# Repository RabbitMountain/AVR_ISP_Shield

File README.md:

(Rabbit Mountain Research) AVR ISP Shield
========================

This shield, once assembled, gives your Arduino a 28-pin ZIF (Zero Insertion Force) socket so it can grab onto unsuspecting ICs. 
The socket and ISP headers are wired to work directly with the ArduinoISP code.

This is a slightly modified clone of the Evil Mad Scientist AVR ISP Shield v2.0. This version is built on the Sparkfun AVR ISP Shield Eagle files, but is more or less an exact clone of the Evil Mad Scientist Shield.

Rabbit Mountain Research changes
-------------------
* converted EvilMadScience design from gEDA to Autodesk EagleCAD
* fixed the non-working "hello" LED
* added 5v / 3v VCC power select jumper (taken from Sparkfun's ISP Shield design)
* added 0.1uF reset capacitor for UNO / 328p Arduino compatibility

Repository Contents
-------------------
* **/Hardware** - All Eagle design files (.brd, .sch)

License Information
-------------------
The hardware is released under [Creative Commons ShareAlike 4.0 International](https://creativecommons.org/licenses/by-sa/4.0/).
Sparkfun Electronics

&

Distributed under the [TAPR Open Hardware License](www.tapr.org/OHL).
Evil Mad Science LCC

Distributed as-is; no warranty is given.

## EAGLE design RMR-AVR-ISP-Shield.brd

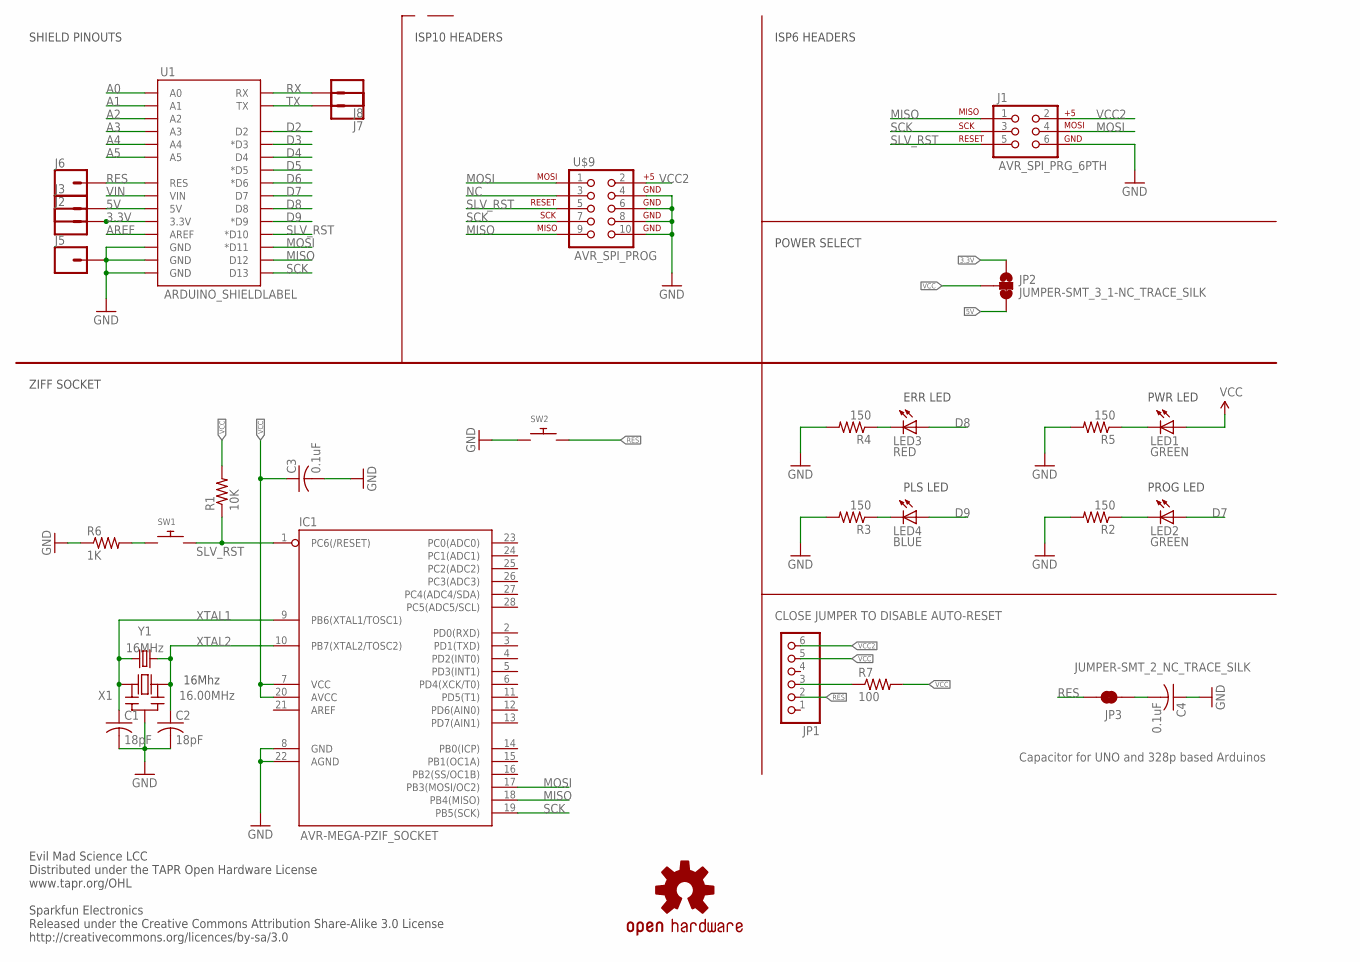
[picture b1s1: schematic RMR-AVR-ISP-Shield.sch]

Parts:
C1, C2: 18pF; C025-024X044
C3, C4: 0.1uF; C025-024X044
IC1: AVR-MEGA-PZIF_SOCKET; DIL28-3-ZIF_SOCKET
J1: AVR_SPI_PRG_6PTH; 2X3
J2, J3, J5, J6, J7, J8: CONN_01; 1X01
JP1: PINHD-1X6/90; 1X06/90
JP2: JUMPER-SMT_3_1-NC_TRACE_SILK; SMT-JUMPER_3_1-NC_TRACE_SILK
JP3: JUMPER-SMT_2_NC_TRACE_SILK; SMT-JUMPER_2_NC_TRACE_SILK
LED1, LED2: GREEN; LED3MM
LED3: RED; LED3MM
LED4: BLUE; LED3MM
R1: 10K; AXIAL-0.4
R2, R3, R4, R5: 150; AXIAL-0.4
R6: 1K; AXIAL-0.4
R7: 100; AXIAL-0.4
SW1, SW2: SWITCH_PUSHBUTTONEVQ-PE; TACT_PANA-EVQ
U1: ARDUINO_SHIELDLABEL; DUEMILANOVE_SHIELD
U$4: OSHW-LOGOM; OSHW-LOGO-M
U$9: AVR_SPI_PROG; AVR_ICSP
X1: 16.00MHz; CERM_OSC
Y1: 16MHz; HC49US

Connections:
3.3V: J2.1, JP2.1, U1.3.3V
5V: J3.1, JP2.3, U1.5V
A0: U1.A0
A1: U1.A1
A2: U1.A2
A3: U1.A3
A4: U1.A4
A5: U1.A5
AREF: U1.AREF
D2: U1.D2
D3: U1.D3 (*D3)
D4: U1.D4
D5: U1.D5 (*D5)
D6: U1.D6 (*D6)
D7: LED2.A, U1.D7
D8: LED3.A, U1.D8
D9: LED4.A, U1.D9 (*D9)
GND: C1.2, C2.2, C3.2, C4.1, IC1.8 (GND), IC1.22 (AGND), J1.6, J5.1, R2.P$2 (2), R3.P$2 (2), R4.P$2 (2), R5.P$2 (2), R6.P$1 (1), SW2.P$1, U1.GND@0 (GND), U1.GND@1 (GND), U1.GND@2 (GND), U$9.4, U$9.6, U$9.8, U$9.10, X1.P$2 (GND)
MISO: IC1.18 (PB4(MISO)), J1.1, U1.D12, U$9.9
MOSI: IC1.17 (PB3(MOSI/OC2)), J1.4, U1.D11 (*D11), U$9.1
unnamed: R6.P$2 (2), SW1.P$1
unnamed: LED2.K (C), R2.P$1 (1)
unnamed: LED3.K (C), R4.P$1 (1)
unnamed: LED1.K (C), R5.P$1 (1)
unnamed: JP1.3, R7.P$1 (1)
unnamed: LED4.K (C), R3.P$1 (1)
unnamed: C4.2, JP3.1
NC: U$9.3
RES: J6.1, JP1.2, JP3.2, SW2.P$2, U1.RES
RX: J8.1, U1.RX
SCK: IC1.19 (PB5(SCK)), J1.3, U1.D13, U$9.7
SLV_RST: IC1.1 (PC6(/RESET)), J1.5, R1.P$1 (1), SW1.P$2, U1.D10 (*D10), U$9.5
TX: J7.1, U1.TX
VCC: C3.1, IC1.7 (VCC), IC1.20 (AVCC), JP1.5, JP2.2, LED1.A, R1.P$2 (2), R7.P$2 (2)
VCC2: J1.2, JP1.6, U$9.2
VIN: U1.VIN
XTAL1: C1.1, IC1.9 (PB6(XTAL1/TOSC1)), X1.P$1 (IN), Y1.1
XTAL2: C2.1, IC1.10 (PB7(XTAL2/TOSC2)), X1.P$3 (OUT), Y1.2

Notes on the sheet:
PWR LED
PROG LED
ISP6 HEADERS
ERR LED
PLS LED
16Mhz
Evil Mad Science LCC Distributed under the TAPR Open Hardware License www.tapr.org/OHL Sparkfun Electronics Released under the Creative Commons Attribution Share-Alike 3.0 License http://creativecommons.org/licences/by-sa/3.0
ZIFF SOCKET
SHIELD PINOUTS
ISP10 HEADERS
CLOSE JUMPER TO DISABLE AUTO-RESET
POWER SELECT
Capacitor for UNO and 328p based Arduinos

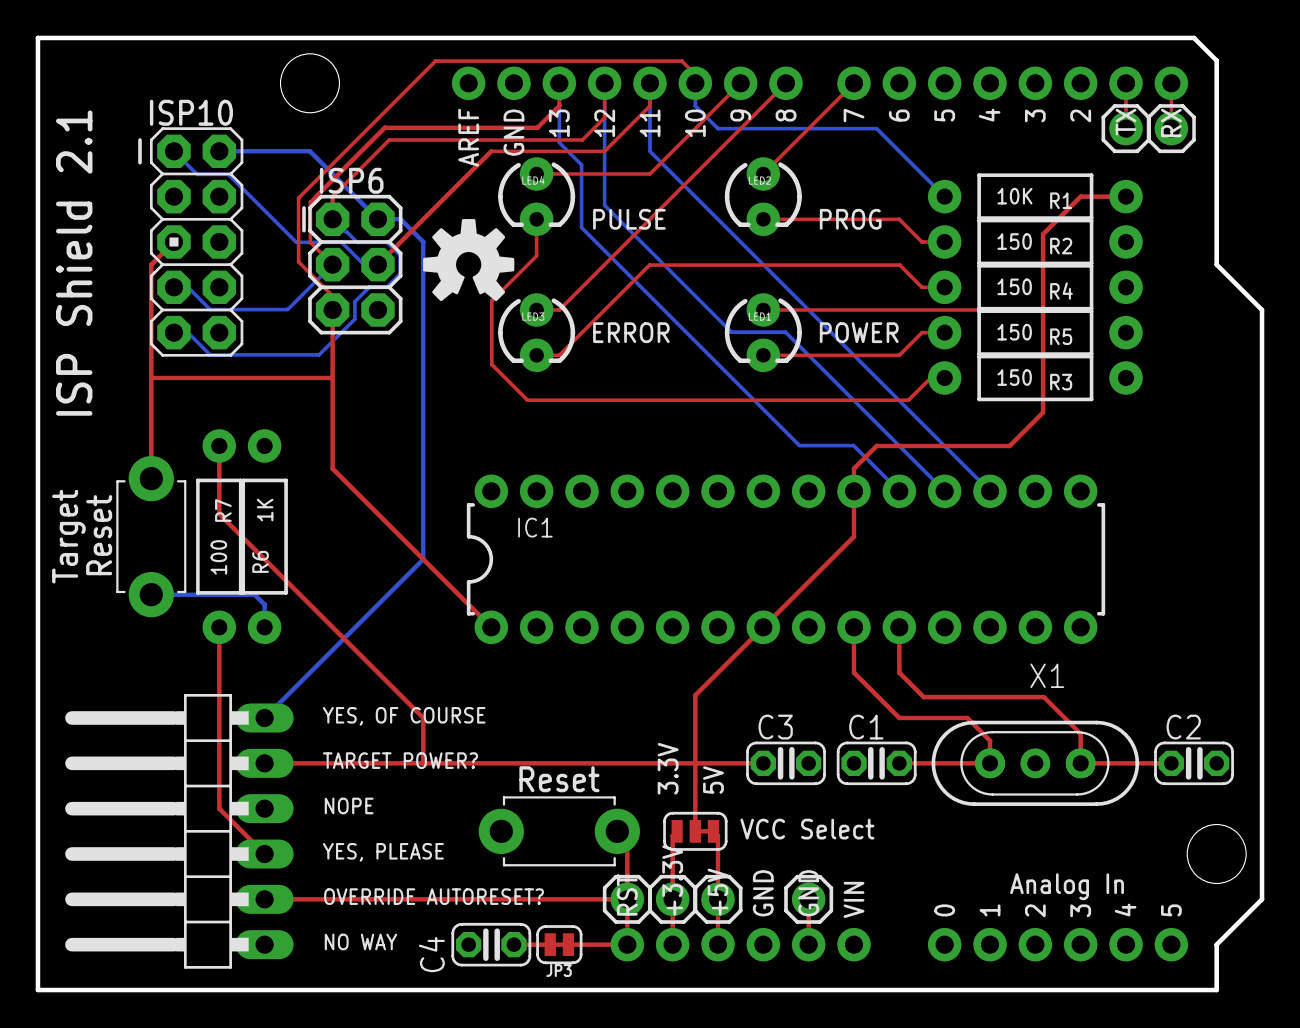
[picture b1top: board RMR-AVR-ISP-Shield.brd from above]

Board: 2 copper layers, 68.6 x 53.3 mm, 33 parts (0 on the bottom side), 24 nets.

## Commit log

2021-08-24 Add files via upload
    changed reset capacitor
2021-08-25 Add files via upload
    added jumper to the reset capacitor for UNO / 328p based Arduinos.

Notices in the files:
parts and their libraries:
SparkFun-Jumpers: Licensing: Creative Commons ShareAlike 4.0 International - https://creativecommons.org/licenses/by-sa/4.0
